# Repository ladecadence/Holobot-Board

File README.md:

# Holobot-Board

KiCAD PCB design fot the Holobot art installation.

See [Holobot repository](https://github.com/ladecadence/Holobot) for more info.

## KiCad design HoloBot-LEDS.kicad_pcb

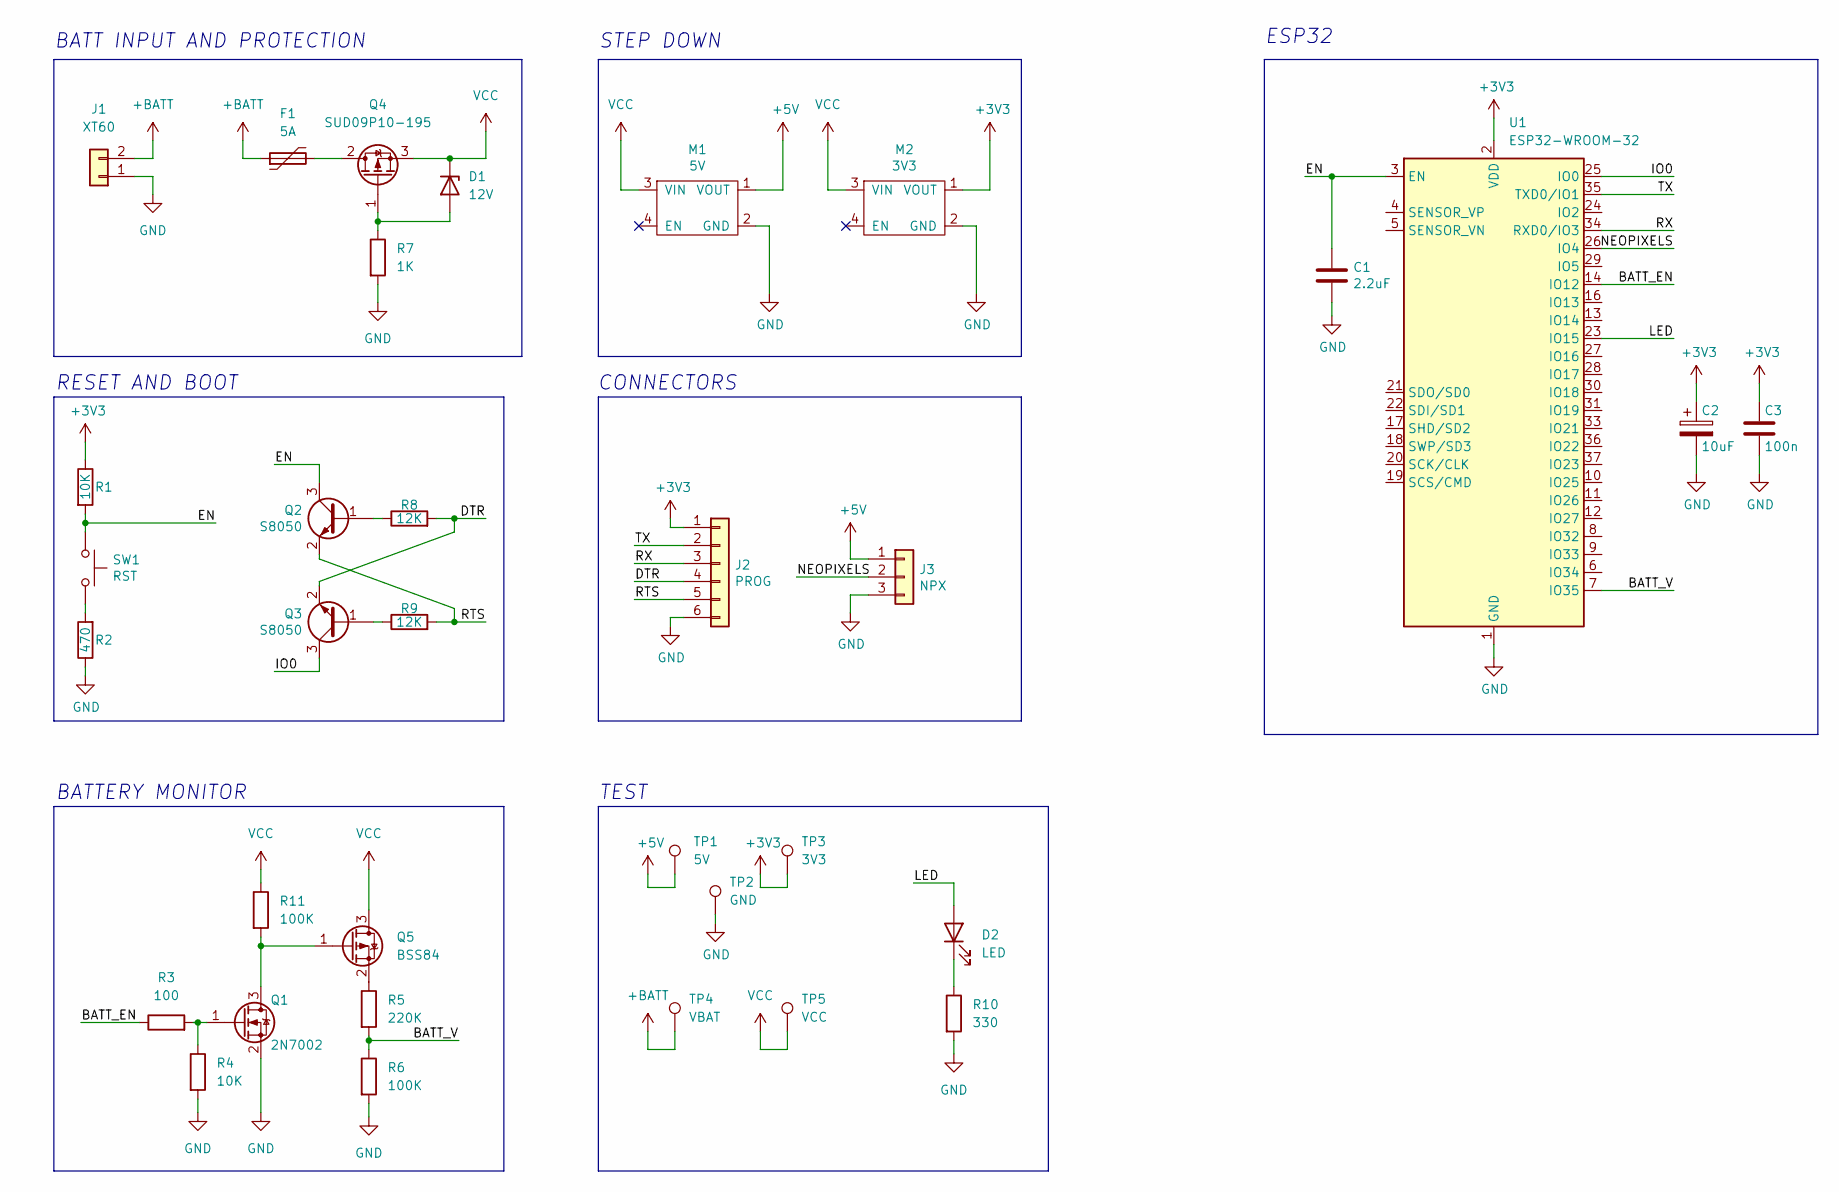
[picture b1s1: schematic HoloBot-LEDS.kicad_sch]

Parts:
C1: 2.2uF; C_0805_2012Metric
C2: 10uF; CP_EIA-3216-18_Kemet-A
C3: 100n; C_0805_2012Metric
D1: 12V; D_SOD-123
D2: LED; LED_0603_1608Metric
F1: 5A; Fuse_1206_3216Metric
J1: XT60; AMASS_XT60-M_1x02_P7.20mm_Vertical
J2: PROG; PinHeader_1x06_P2.54mm_Vertical
J3: NPX; Molex_KK-254_AE-6410-03A_1x03_P2.54mm_Vertical
M1: 5V; MiniStepDown
M2: 3V3; MiniStepDown
Q1: 2N7002; SOT-23
Q2, Q3: S8050; SOT-23
Q4: SUD09P10-195; TO-252-2
Q5: BSS84; SOT-23
R1: 10K; R_0805_2012Metric
R2: 470; R_0805_2012Metric
R3: 100; R_0603_1608Metric
R4: 10K; R_0603_1608Metric
R5: 220K; R_0603_1608Metric
R6, R11: 100K; R_0603_1608Metric
R7: 1K; R_0603_1608Metric
R8, R9: 12K; R_0603_1608Metric
R10: 330; R_0603_1608Metric
SW1: RST; SW_Push_SPST_NO_Alps_SKRK
TP1: 5V; TestPoint_Pad_D1.0mm
TP2: GND; TestPoint_Pad_D1.0mm
TP3: 3V3; TestPoint_Pad_D1.0mm
TP4: VBAT; TestPoint_Pad_D1.0mm
TP5: VCC; TestPoint_Pad_D1.0mm
U1: ESP32-WROOM-32

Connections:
+3V3: C2.1, C3.1, J2.1, M2.1 (VOUT), R1.1, TP3.1, U1.2 (VDD)
+5V: J3.1, M1.1 (VOUT), TP1.1
+BATT: F1.1, J1.2, TP4.1
/BATT_EN: R3.1, U1.14 (IO12)
/BATT_V: R5.2, R6.1, U1.7 (IO35)
/DTR: J2.4, Q3.2 (E), R8.2
/EN: C1.1, Q2.3 (C), R1.2, SW1.1, U1.3 (EN)
/IO0: Q3.3 (C), U1.25 (IO0)
/LED: D2.2 (A), U1.23 (IO15)
/NEOPIXELS: J3.2, U1.26 (IO4)
/RTS: J2.5, Q2.2 (E), R9.2
/RX: J2.3, U1.34 (RXD0/IO3)
/TX: J2.2, U1.35 (TXD0/IO1)
GND: C1.2, C2.2, C3.2, J1.1, J2.6, J3.3, M1.2 (GND), M2.2 (GND), Q1.2 (S), R2.1, R4.2, R6.2, R7.2, R10.2, TP2.1, U1.1 (GND), U1.15 (GND), U1.38 (GND), U1.39 (GND)
unnamed: D1.2 (A), Q4.1 (G), R7.1
unnamed: D2.1 (K), R10.1
unnamed: F1.2, Q4.2 (D)
unnamed: Q1.3 (D), Q5.1 (G), R11.2
unnamed: Q2.1 (B), R8.1
unnamed: Q3.1 (B), R9.1
unnamed: R2.2, SW1.2
unnamed: Q1.1 (G), R3.2, R4.1
unnamed: Q5.2 (S), R5.1
VCC: D1.1 (K), M1.3 (VIN), M2.3 (VIN), Q4.3 (S), Q5.3 (D), R11.1, TP5.1

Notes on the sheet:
CONNECTORS
STEP DOWN
TEST
ESP32
BATT INPUT AND PROTECTION
RESET AND BOOT
BATTERY MONITOR

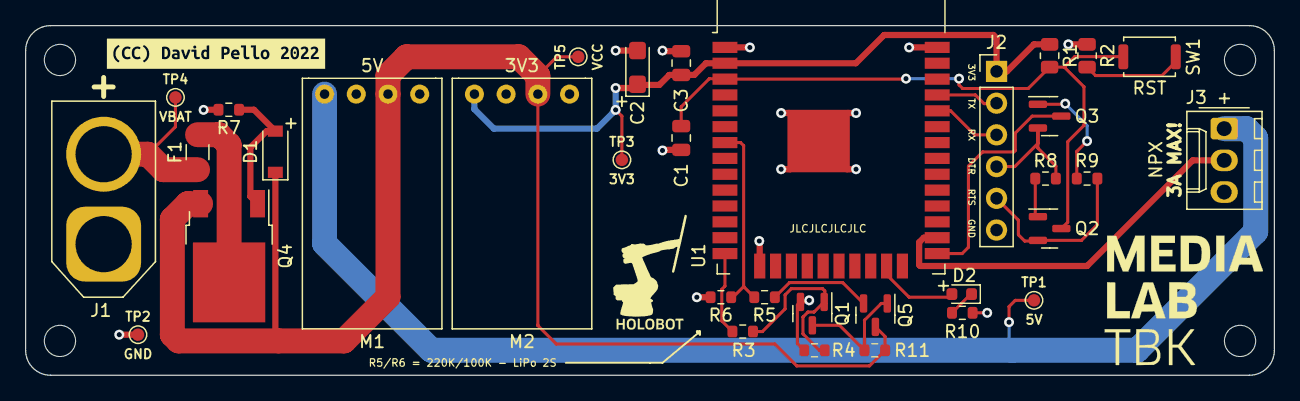
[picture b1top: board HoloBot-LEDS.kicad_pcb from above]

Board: 2 copper layers, 100.0 x 28.0 mm, 35 parts (0 on the bottom side), 24 nets.

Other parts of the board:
kibuzzard-62309EA5: G***; kibuzzard-62309EA5

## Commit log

2022-06-08 Initial upload
